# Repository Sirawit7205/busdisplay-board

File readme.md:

# Busdisplay

This is an open-source KiCad design files for a circuit that could be connected to an 8-bit bus to monitor the value on it in decimal or hexadecimal.

## The board

The board is 33x50mm (perfect for 3x2 panel). Featuring:

- PIC16F570 Microcontroller + ICSP header
- 74HCT245 Transceiver as an input buffer
- 3-digit 7-segment Display
- Hex/Dec Selector Header
- Power and Data Input Headers

We are currently at Revision 3. Changelog is below:

**Revision 3 (June 2021)**

 - Replaced PIC16F57 with PIC16F570, cheaper and more powerful.
 - Removed an external crystal because new PIC now has internal oscillator.
 - Removed buffer chip disable header, nothing shares ICSP pins now.
 - Added a bulk capacitor.
 - Redone the PCB again because new PIC has very different pinout.

**Revision 2 (May 2021)**
 - Added a header to disable the buffer chip, which would then allow the ICSP header to work.
 - Added a pull-up resistor for Selector Header.
 - Replaced HC-49 4MHz crystal with 5032 8Mhz crystal.
 - Replaced an 74HCT244 with 74HCT245 for easier routing.
 - Redone the PCB so every parts are on the top layer, and that the mosfets are not under the display.
 
**Revision 1 (January 2020)**
- Initial Design on [EasyEDA](https://easyeda.com/lsirawit24/8-bit-display)
- This version has several mistakes, for example, the ICSP header does not work, and the pull-up/down resistor is missing on Selector Header.

## What is provided

The goal of this repository is to enable you to build this on your own as easy as possible (although I originally plan to sell this as a kit as well). **I've included all of the schematics, gerbers, BOMs, and display driver firmware for you to use.** 

Hardware is licensed under `SPDX-License-Identifier: CERN-OHL-S-2.0`

Software is licensed under `SPDX-License-Identifier: GPL`

Documentation is licensed under `SPDX-License-Identifier: CC-BY-SA-4.0`

**This project is an OSHWA Certified Open Source Hardware Project with UID [TH000009](https://certification.oshwa.org/th000009.html).**

Unfortunately. I have to excluded the 3D models use to render the board in KiCAD because I don't know how each of them was licensed. They are all from GrabCad and you could search and download them by yourself.

**Note: Due to this, there might be a popup warning you about "3D model Search Path" in PCBNew. I honestly don't know how to fix this but it will not affect any KiCAD functionality.**

## Credits

 - 3-digit LED Display model by Robert Dee: https://grabcad.com/library/3-digit-led-display-1
 - Pin header and Jumpers model by singlefonts: https://grabcad.com/library/pin-header-and-jumper-1
 - SOIC package collection by Egor Chugay: https://grabcad.com/library/soic-package-collection-1/details?folder_id=5653384

> Written with [StackEdit](https://stackedit.io/).

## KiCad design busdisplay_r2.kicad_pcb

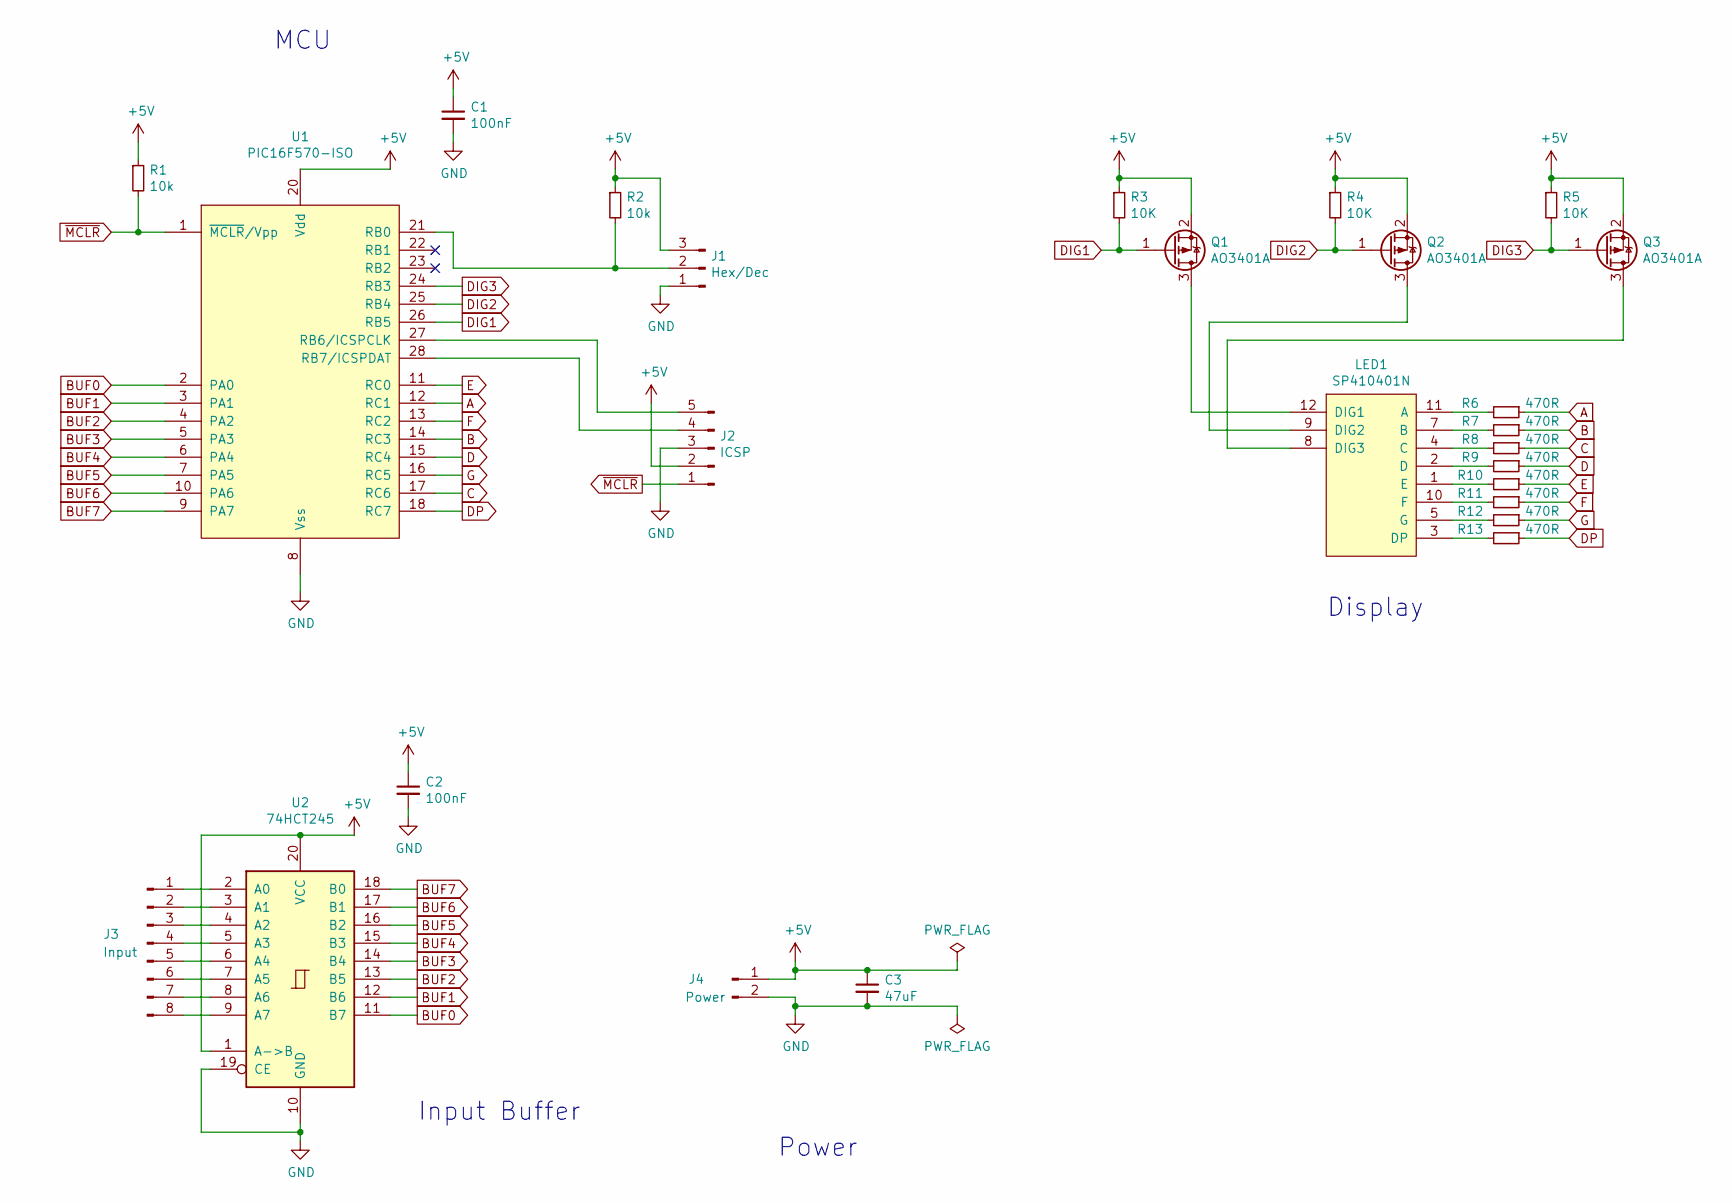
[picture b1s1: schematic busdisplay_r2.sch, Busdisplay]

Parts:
C1, C2: 100nF; C_0603_1608Metric
C3: 47uF; C_1206_3216Metric
J1: Hex/Dec; PinHeader_1x03_P2.54mm_Vertical
J2: ICSP; PinHeader_1x05_P2.54mm_Vertical
J3: Input; PinHeader_1x08_P2.54mm_Vertical
J4: Power; PinHeader_1x02_P2.54mm_Vertical
LED1: SP410401N
Q1, Q2, Q3: AO3401A; SOT-23
R1, R2: 10k; R_0603_1608Metric
R3, R4, R5: 10K; R_0603_1608Metric
R6, R7, R8, R9, R10, R11, R12, R13: 470R; R_0603_1608Metric
U1: PIC16F570-ISO; SOIC-28W_7.5x17.9mm_P1.27mm
U2: 74HCT245; SO-20_5.3x12.6mm_P1.27mm

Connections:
+5V: C1.1, C2.1, C3.1, J1.3, J2.2, J4.1, Q1.2 (S), Q2.2 (S), Q3.2 (S), R1.1, R2.1, R3.1, R4.1, R5.1, U1.20 (Vdd), U2.1 (A->B), U2.20 (VCC)
A: R6.1, U1.12 (RC1)
B: R7.1, U1.14 (RC3)
BUF0: U1.2 (PA0), U2.11 (B7)
BUF1: U1.3 (PA1), U2.12 (B6)
BUF2: U1.4 (PA2), U2.13 (B5)
BUF3: U1.5 (PA3), U2.14 (B4)
BUF4: U1.6 (PA4), U2.15 (B3)
BUF5: U1.7 (PA5), U2.16 (B2)
BUF6: U1.10 (PA6), U2.17 (B1)
BUF7: U1.9 (PA7), U2.18 (B0)
C: R8.1, U1.17 (RC6)
D: R9.1, U1.15 (RC4)
DIG1: Q1.1 (G), R3.2, U1.26 (RB5)
DIG2: Q2.1 (G), R4.2, U1.25 (RB4)
DIG3: Q3.1 (G), R5.2, U1.24 (RB3)
DP: R13.1, U1.18 (RC7)
E: R10.1, U1.11 (RC0)
F: R11.1, U1.13 (RC2)
G: R12.1, U1.16 (RC5)
GND: C1.2, C2.2, C3.2, J1.1, J2.3, J4.2, U1.8 (Vss), U1.19 (Vss), U2.10 (GND), U2.19 (CE)
unnamed: J1.2, R2.2, U1.21 (RB0)
unnamed: J2.4, U1.28 (RB7/ICSPDAT)
unnamed: J2.5, U1.27 (RB6/ICSPCLK)
unnamed: J3.1, U2.2 (A0)
unnamed: J3.2, U2.3 (A1)
unnamed: J3.3, U2.4 (A2)
unnamed: J3.4, U2.5 (A3)
unnamed: J3.5, U2.6 (A4)
unnamed: J3.6, U2.7 (A5)
unnamed: J3.7, U2.8 (A6)
unnamed: J3.8, U2.9 (A7)
unnamed: LED1.1 (E), R10.2
unnamed: LED1.2 (D), R9.2
unnamed: LED1.3 (DP), R13.2
unnamed: LED1.4 (C), R8.2
unnamed: LED1.5 (G), R12.2
unnamed: LED1.7 (B), R7.2
unnamed: LED1.8 (DIG3), Q3.3 (D)
unnamed: LED1.9 (DIG2), Q2.3 (D)
unnamed: LED1.10 (F), R11.2
unnamed: LED1.11 (A), R6.2
unnamed: LED1.12 (DIG1), Q1.3 (D)
~MCLR: J2.1, R1.2, U1.1 (~MCLR~/Vpp)

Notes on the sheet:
Display
MCU
Input Buffer
Power

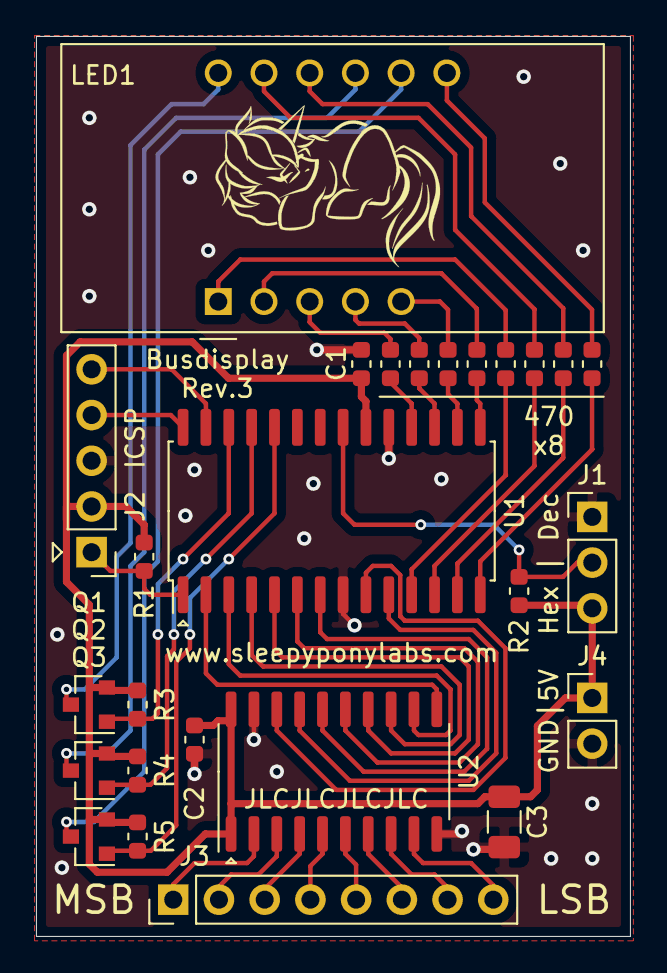
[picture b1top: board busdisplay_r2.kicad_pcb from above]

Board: 2 copper layers, 33.0 x 50.0 mm, 26 parts (0 on the bottom side), 44 nets.

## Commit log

2021-06-06 Revision 2 of the board
2021-06-06 Revision 3 files
2021-06-06 Add missing assets
2021-09-01 Add firmware, gerbers and ibom
2021-09-01 Update readme and image
2021-09-01 rename some files
2022-05-11 Update DFP, Reduce delay for better refresh rate
2023-05-25 Update readme.md
    Update licenses and add OSHWA info.
2023-05-28 Create LICENSE
